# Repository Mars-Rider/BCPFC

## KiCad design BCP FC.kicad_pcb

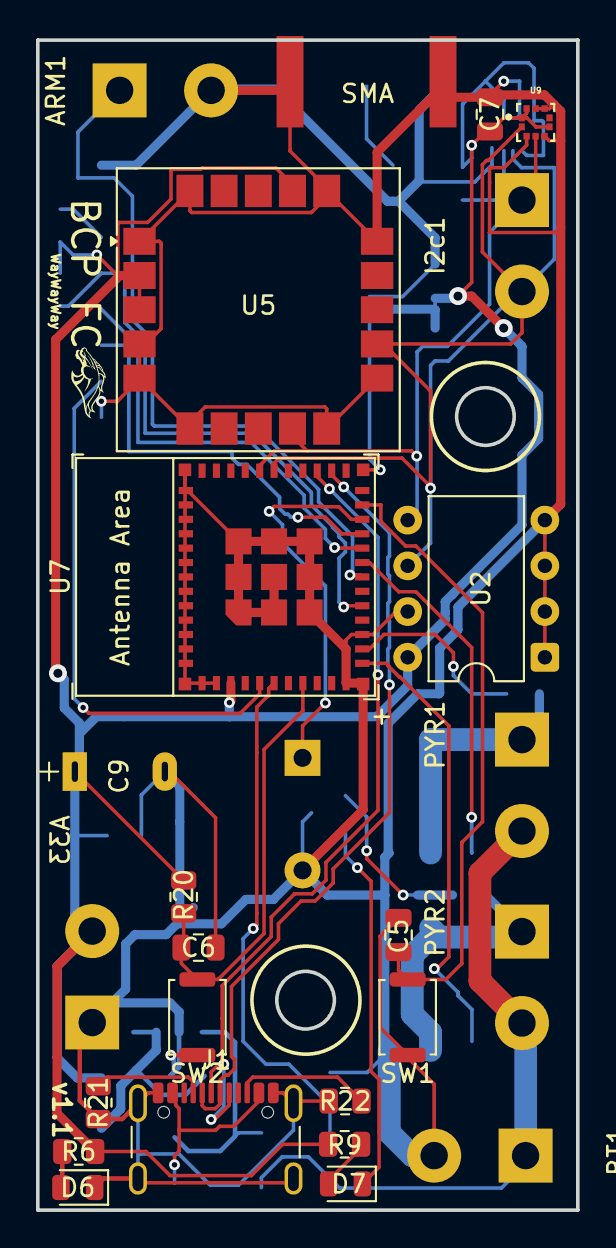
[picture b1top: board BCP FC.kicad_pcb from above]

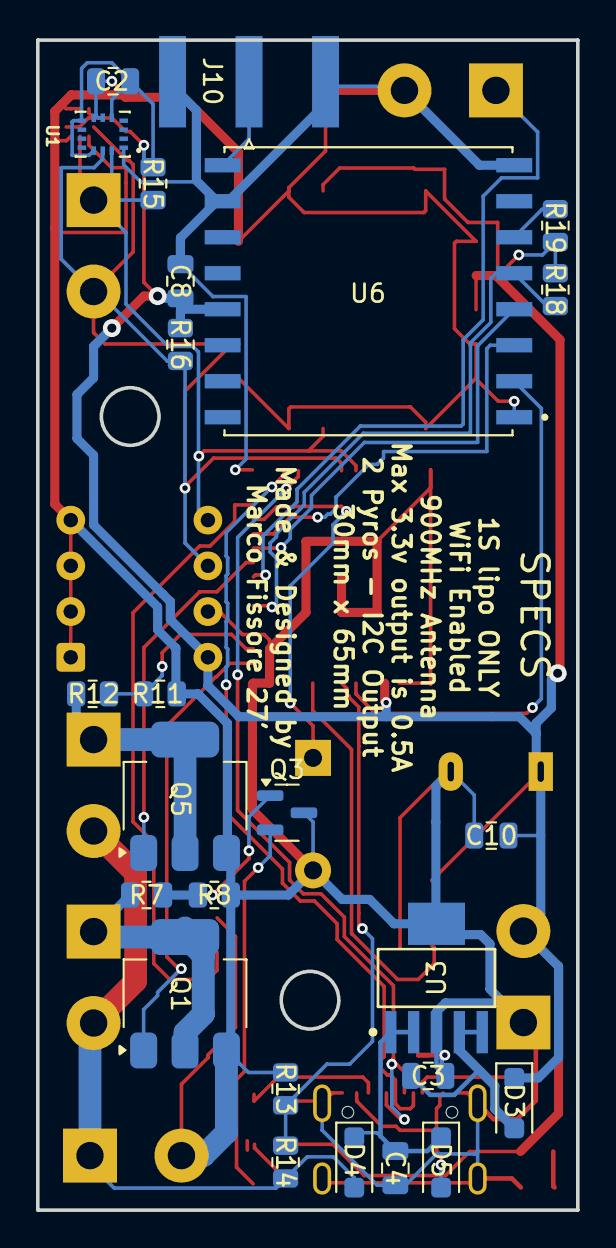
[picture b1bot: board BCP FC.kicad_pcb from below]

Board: 2 copper layers, 30.0 x 65.0 mm, 50 parts (25 on the bottom side), 32 nets.

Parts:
A33: Screw_Terminal_01x02; TerminalBlock_bornier-2_P5.08mm
ARM1: Screw_Terminal_01x02; TerminalBlock_bornier-2_P5.08mm
BT1: Battery; TerminalBlock_bornier-2_P5.08mm
BZ1: Buzzer; Buzzer_12x8.5
C2, C5, C7: 0.1uF; C_0805_2012Metric
C3, C4, C8, C10: 10uF; C_0805_2012Metric
C6: 1uF; C_0805_2012Metric
C9: PTKL554P
D3, D4, D5: MBR1020VL; D_SOD-123F
D6: GENERIC GREEN; LED_0805_2012Metric
D7: GENERIC ORANGE; LED_0805_2012Metric
I2c1: Screw_Terminal_01x02; TerminalBlock_bornier-2_P5.08mm
J1: USB_C_Receptacle_USB2.0_16P; USB_C_Receptacle_GCT_USB4105-xx-A_16P_TopMnt_Horizontal
J10: Conn_Coaxial; SMA_Amphenol_132289_EdgeMount
PYR1, PYR2: Screw_Terminal_01x02; TerminalBlock_bornier-2_P5.08mm
Q1, Q5: NDT3055L; SOT-223-3_TabPin2
Q3: MMBT2222A; SOT-23
R6, R9: 120; R_0805_2012Metric
R7, R8, R11, R12, R13, R14, R20: 10k; R_0805_2012Metric
R15, R16: 4.7k; R_0805_2012Metric
R18, R19: 10K; R_0805_2012Metric
R21, R22: 5.1K; R_0805_2012Metric
SW1, SW2: SW_Push; SW_Push_SPST_NO_Alps_SKRK
U1: BMI270; XDCR_BMI270
U2: 24LC128; DIP-8_W7.62mm_Socket
U3: TPS7A4533DCQT; DCQ0006A-IPC_A
U5: SAM-M8Q; ublox_SAM-M8Q
U6: RFM95W-915S2; MODULE_RFM96W-433S2
U7: ESP32-C3-MINI-1
U9: BMP388; PQFN50P200X200X80-10N

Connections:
+3V3: A33.2, C2.1, C7.1, C8.1, C9.1, C10.1, D3.1 (K), R6.2, R9.2, R15.1, R16.1, R18.1, R19.1, R20.1, U1.5 (VDDIO), U1.8 (VDD), U1.12 (CSB), U2.8 (VCC), U5.2 (VCC_IO), U5.3 (V_BCKP), U5.17 (VCC), U6.13 (3.3V), U7.3 (3V3), U9.1 (VDDIO), U9.6 (CSB), U9.10 (VDD)
+5V: D5.2 (A), J1.A4 (VBUS), J1.A9 (VBUS), J1.B4 (VBUS), J1.B9 (VBUS)
+BATT: BT1.1 (+), D4.2 (A), PYR1.2, PYR2.2, R14.1
/ARM: ARM1.1, U7.18 (GPIO4/ADC1_CH4)
/BOOT: C5.2, SW1.2, U7.23 (GPIO9)
/BZZ: BZ1.1 (+), U7.22 (GPIO8)
/CLK: U6.4 (SCK), U7.20 (GPIO6)
/CNT 1: R11.2, R12.2, U7.13 (GPIO1/ADC1_CH1/XTAL_32K_N)
/CNT 2: Q3.1 (B), R7.2, R8.2
/CS: R18.2, U6.5 (NSS), U7.16 (GPIO10)
/EN: C6.2, R20.2, SW2.2, U7.8 (EN/CHIP_PU)
/MISO: U6.2 (MISO), U7.5 (GPIO2/ADC1_CH2)
/MOSI: U6.3 (MOSI), U7.21 (GPIO7)
/PYR 1: Q5.1 (G), U7.19 (GPIO5/ADC2_CH0)
/PYR 2: Q1.1 (G), U7.12 (GPIO0/ADC1_CH0/XTAL_32K_P)
/SBAT: R13.2, R14.2, U7.6 (GPIO3/ADC1_CH3)
/SCL: I2c1.2, R16.2, U1.13 (SCX), U2.6 (SCL), U5.12 (SCL), U7.30 (GPIO20/U0RXD), U9.2 (SCK)
/SDA: I2c1.1, R15.2, U1.14 (SDX), U2.5 (SDA), U5.9 (SDA), U7.31 (GPIO21/U0TXD), U9.4 (SDI)
GND: A33.1, ARM1.2, BT1.2 (-), BZ1.2 (-), C2.2, C3.2, C4.2, C5.1, C6.1, C7.2, C8.2, C9.2, C10.2, D6.1 (K), J1.A1 (GND), J1.A12 (GND), J1.B1 (GND), J1.B12 (GND), J1.S1 (SHIELD), J10.2 (Ext), Q1.3 (S), Q3.3 (C), Q5.3 (S), R8.1, R11.1, R13.1, R21.1, R22.1, SW1.1, SW2.1, U1.1 (SDO), U1.6 (GNDIO), U1.7 (GND), U2.1 (A0), U2.2 (A1), U2.3 (A2), U2.4 (GND), U2.7 (WP), U3.3 (GND), U3.6 (GND), U5.1 (GND), U5.4 (GND), U5.5 (GND), U5.6 (GND), U5.10 (GND), U5.11 (GND), U5.15 (GND), U5.16 (GND), U5.20 (GND), U6.1 (GND), U6.8 (GND), U6.10 (GND), U7.1 (GND), U7.2 (GND), U7.11 (GND), U7.14 (GND), U7.36 (GND), U7.37 (GND), U7.38 (GND), U7.39 (GND), U7.40 (GND), U7.41 (GND), U7.42 (GND), U7.43 (GND), U7.44 (GND), U7.45 (GND), U7.46 (GND), U7.47 (GND), U7.48 (GND), U7.49 (GND), U7.50 (GND), U7.51 (GND), U7.52 (GND), U7.53 (GND), U9.3 (VSS), U9.5 (SDO), U9.8 (VSS), U9.9 (VSS)
unnamed: C3.1, D3.2 (A), U3.4 (OUT), U3.5 (ADJ)
unnamed: C4.1, D4.1 (K), D5.1 (K), U3.1 (SHDN_N), U3.2 (IN)
unnamed: D6.2 (A), R6.1
unnamed: D7.2 (A), R9.1
unnamed: D7.1 (K), Q3.2 (E)
unnamed: J1.A5 (CC1), R21.2
unnamed: J1.B5 (CC2), R22.2
unnamed: J10.1 (In), U6.9 (ANT)
unnamed: PYR1.1, Q5.2 (D), R12.1
unnamed: PYR2.1, Q1.2 (D), R7.1
unnamed: R19.2, U6.6 (RESET)
unnamed: J1.A7 (D-), J1.B7 (D-), U7.26 (GPIO18/USB_D-)
unnamed: J1.A6 (D+), J1.B6 (D+), U7.27 (GPIO19/USB_D+)

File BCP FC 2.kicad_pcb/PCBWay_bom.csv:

Designator,Quantity,Value,Footprint,Package,MPN,DNP,Mount_Type,Description,Sim.Pins,PATREV,MF,MAXIMUM_PACKAGE_HEIGHT,Price,Check_prices,STANDARD,SnapEDA_Link,MP,Description_1,Availability,MANUFACTURER,PARTREV
"C10, C8",2,10uF,C_0805_2012Metric,,,,smt,Unpolarized capacitor,,,,,,,,,,,,,
"C11, C2, C5, C7",4,0.1uF,C_0805_2012Metric,,,,smt,Unpolarized capacitor,,,,,,,,,,,,,
"C3, C4, C6",3,1uF,C_0805_2012Metric,,,,smt,Unpolarized capacitor,,,,,,,,,,,,,
"D3, D4, D5",3,MBR1020VL,D_SOD-123F,,,,smt,"20V, 1A, 340 mV, Schottky Diode Rectifier, SOD-123F",,,,,,,,,,,,,
D6,1,GENERIC GREEN,LED_0805_2012Metric,,,,smt,Light emitting diode,1=K 2=A,,,,,,,,,,,,
D7,1,GENERIC YELLOW,LED_0805_2012Metric,,,,smt,Light emitting diode,1=K 2=A,,,,,,,,,,,,
J10,1,Conn_Coaxial,SMA_Amphenol_132289_EdgeMount,,,,smt,"coaxial connector (BNC, SMA, SMB, SMC, Cinch/RCA, LEMO, ...)",,,,,,,,,,,,,
P1,1,USB_C_Plug_USB2.0,USB_C_Receptacle_GCT_USB4105-xx-A_16P_TopMnt_Horizontal,,,,smt,USB 2.0-only Type-C Plug connector,,,,,,,,,,,,,
"Q1, Q5",2,NDT3055L,SOT-223-3_TabPin2,,,,smt,"4A Id, 60V Vds, N-Channel Logic Level Enhancement Mode MOSFET, SOT-223",,,,,,,,,,,,,
Q3,1,MMBT2222A,SOT-23,,,,smt,"600mA Ic, 40V Vce, NPN Transistor, SOT-23",,,,,,,,,,,,,
"R11, R12, R13, R14, R20, R7, R8",7,10k,R_0805_2012Metric,,,,smt,"Resistor, US symbol",,,,,,,,,,,,,
"R15, R16",2,4.7k,R_0805_2012Metric,,,,smt,"Resistor, US symbol",,,,,,,,,,,,,
"R18, R19",2,10K,R_0805_2012Metric,,,,smt,"Resistor, US symbol",,,,,,,,,,,,,
"R6, R9",2,120,R_0805_2012Metric,,,,smt,"Resistor, US symbol",,,,,,,,,,,,,
"SW1, SW2",2,SW_Push,SW_Push_SPST_NO_Alps_SKRK,,,,smt,"Push button switch, generic, two pins",,,,,,,,,,,,,
U1,1,BMI270,XDCR_BMI270,LGA-14 Bosch Sensortec,,,smt,,,1.0,Bosch Sensortec,0.87mm,None,https://www.snapeda.com/parts/BMI270/Bosch/view-part/?ref=eda,Manufacturer Recommendations,https://www.snapeda.com/parts/BMI270/Bosch/view-part/?ref=snap,BMI270,"Accelerometer, Gyroscope, 6 Axis Sensor I2C, SPI Output",In Stock,Bosch Sensortec,
U3,1,RFM96W-433S2,MODULE_RFM96W-433S2,,,,smt,"Low power long range transceiver module, SPI and parallel interface, 433 MHz, spreading factor 6 to12, bandwidth 7.8 to 500kHz, -111 to -148 dBm, SMD-16, DIP-16",,,,,,,,,,,,,
U4,1,TPS73733DCQR,IC_TPS73733DCQR,,,,tht,,,,,1.8 mm,,,Manufacturer Recommendations,,,,,Texas Instruments,R
U5,1,SAM-M8Q,ublox_SAM-M8Q,,,,smt,GPS ublox M8 variant,,,,,,,,,,,,,
U7,1,ESP32-C3-MINI-1,ESP32-C3-MINI-1,,,,smt,ESP32-C3-MINI-1 family is an ultra-low-power MCU-based SoC solution that supports 2.4 GHz Wi-Fi and Bluetooth®Low Energy (Bluetooth LE).,,,,,,,,,,,,,
U9,1,BMP388,PQFN50P200X200X80-10N,WFLGA-10 Bosch Tools,,,smt,,,,Bosch Sensortec,,None,https://www.snapeda.com/parts/BMP388/Bosch/view-part/?ref=eda,IPC 7351B,https://www.snapeda.com/parts/BMP388/Bosch/view-part/?ref=snap,BMP388,Pressure Sensor 4.35PSI ~ 18.13PSI (30kPa ~ 125kPa) Absolute - - 10-WFLGA,In Stock,BOSCH,1.1

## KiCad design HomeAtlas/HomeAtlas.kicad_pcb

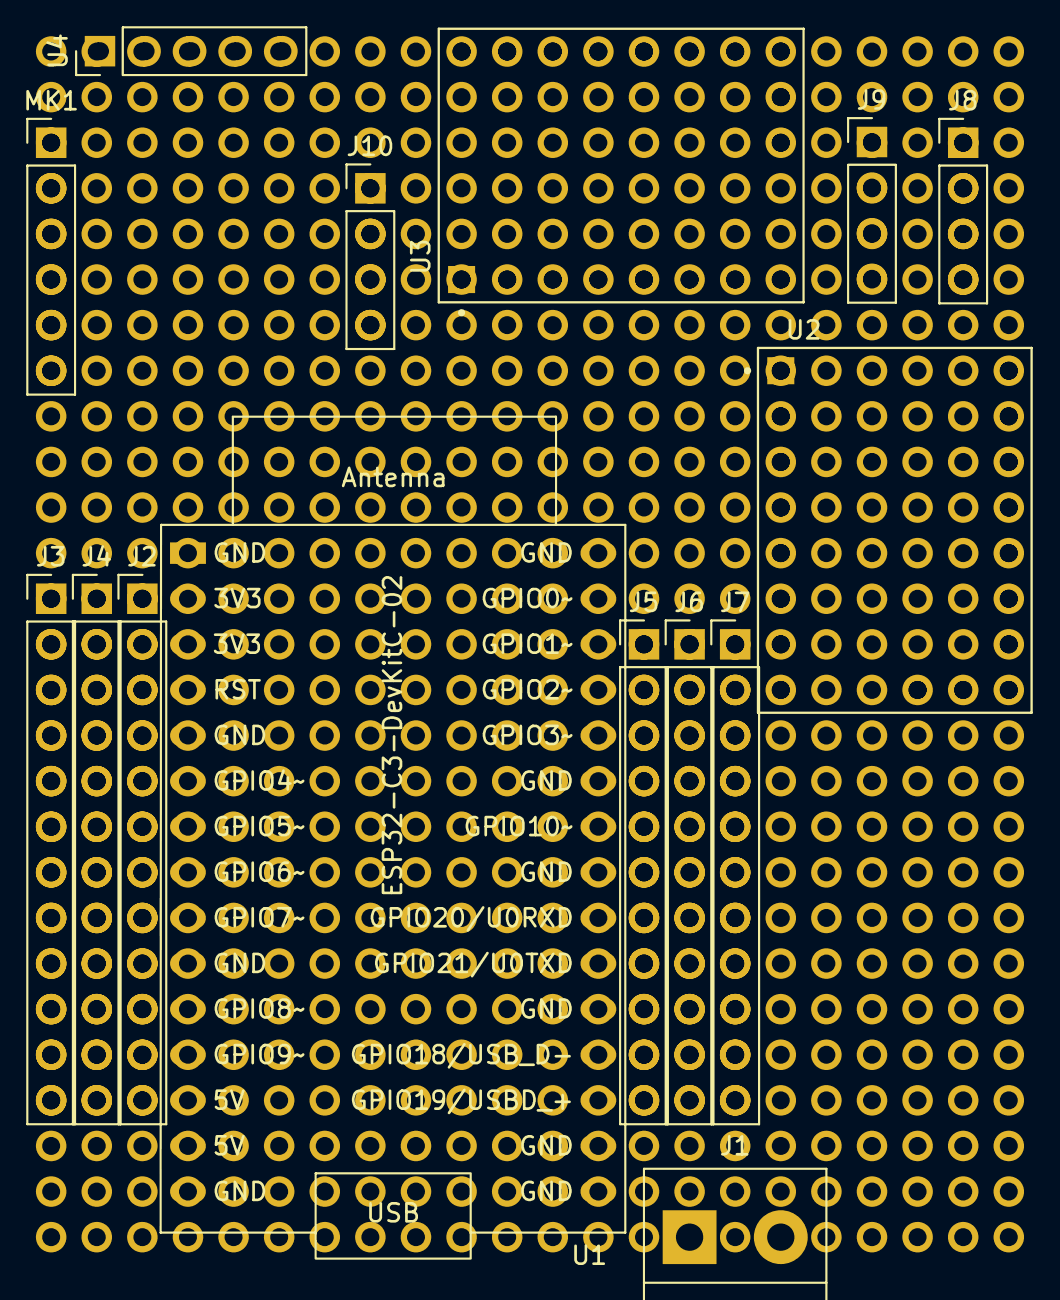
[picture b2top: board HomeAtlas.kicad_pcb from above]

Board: 2 copper layers, 15 parts (0 on the bottom side), 4 nets, no tracks yet.

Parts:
J1: Screw_Terminal_01x02; TerminalBlock_bornier-2_P5.08mm
J2, J3, J4: Conn_01x12; PinHeader_1x12_P2.54mm_Vertical
J5, J6, J7: Conn_01x11; PinHeader_1x11_P2.54mm_Vertical
J8, J9, J10: Conn_01x04; PinHeader_1x04_P2.54mm_Vertical
MK1: ICS-43434; PinHeader_1x06_P2.54mm_Vertical
U1: ESP32-C3-DevKitC-02
U2, U3: TMC2209_SILENTSTEPSTICK; MODULE_TMC2209_SILENTSTEPSTICK
U4: DS1307+; PinHeader_1x05_P2.54mm_Vertical

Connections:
3V3: U1.2 (3V3), U1.3 (3V3)
5V: U1.13 (5V), U1.14 (5V)
GND: U2.1 (GND), U2.7 (GND), U3.1 (GND), U3.7 (GND)
unnamed: U1.1 (GND), U1.5 (GND), U1.10 (GND), U1.15 (GND), U1.16 (GND), U1.17 (GND), U1.20 (GND), U1.23 (GND), U1.25 (GND), U1.30 (GND)
